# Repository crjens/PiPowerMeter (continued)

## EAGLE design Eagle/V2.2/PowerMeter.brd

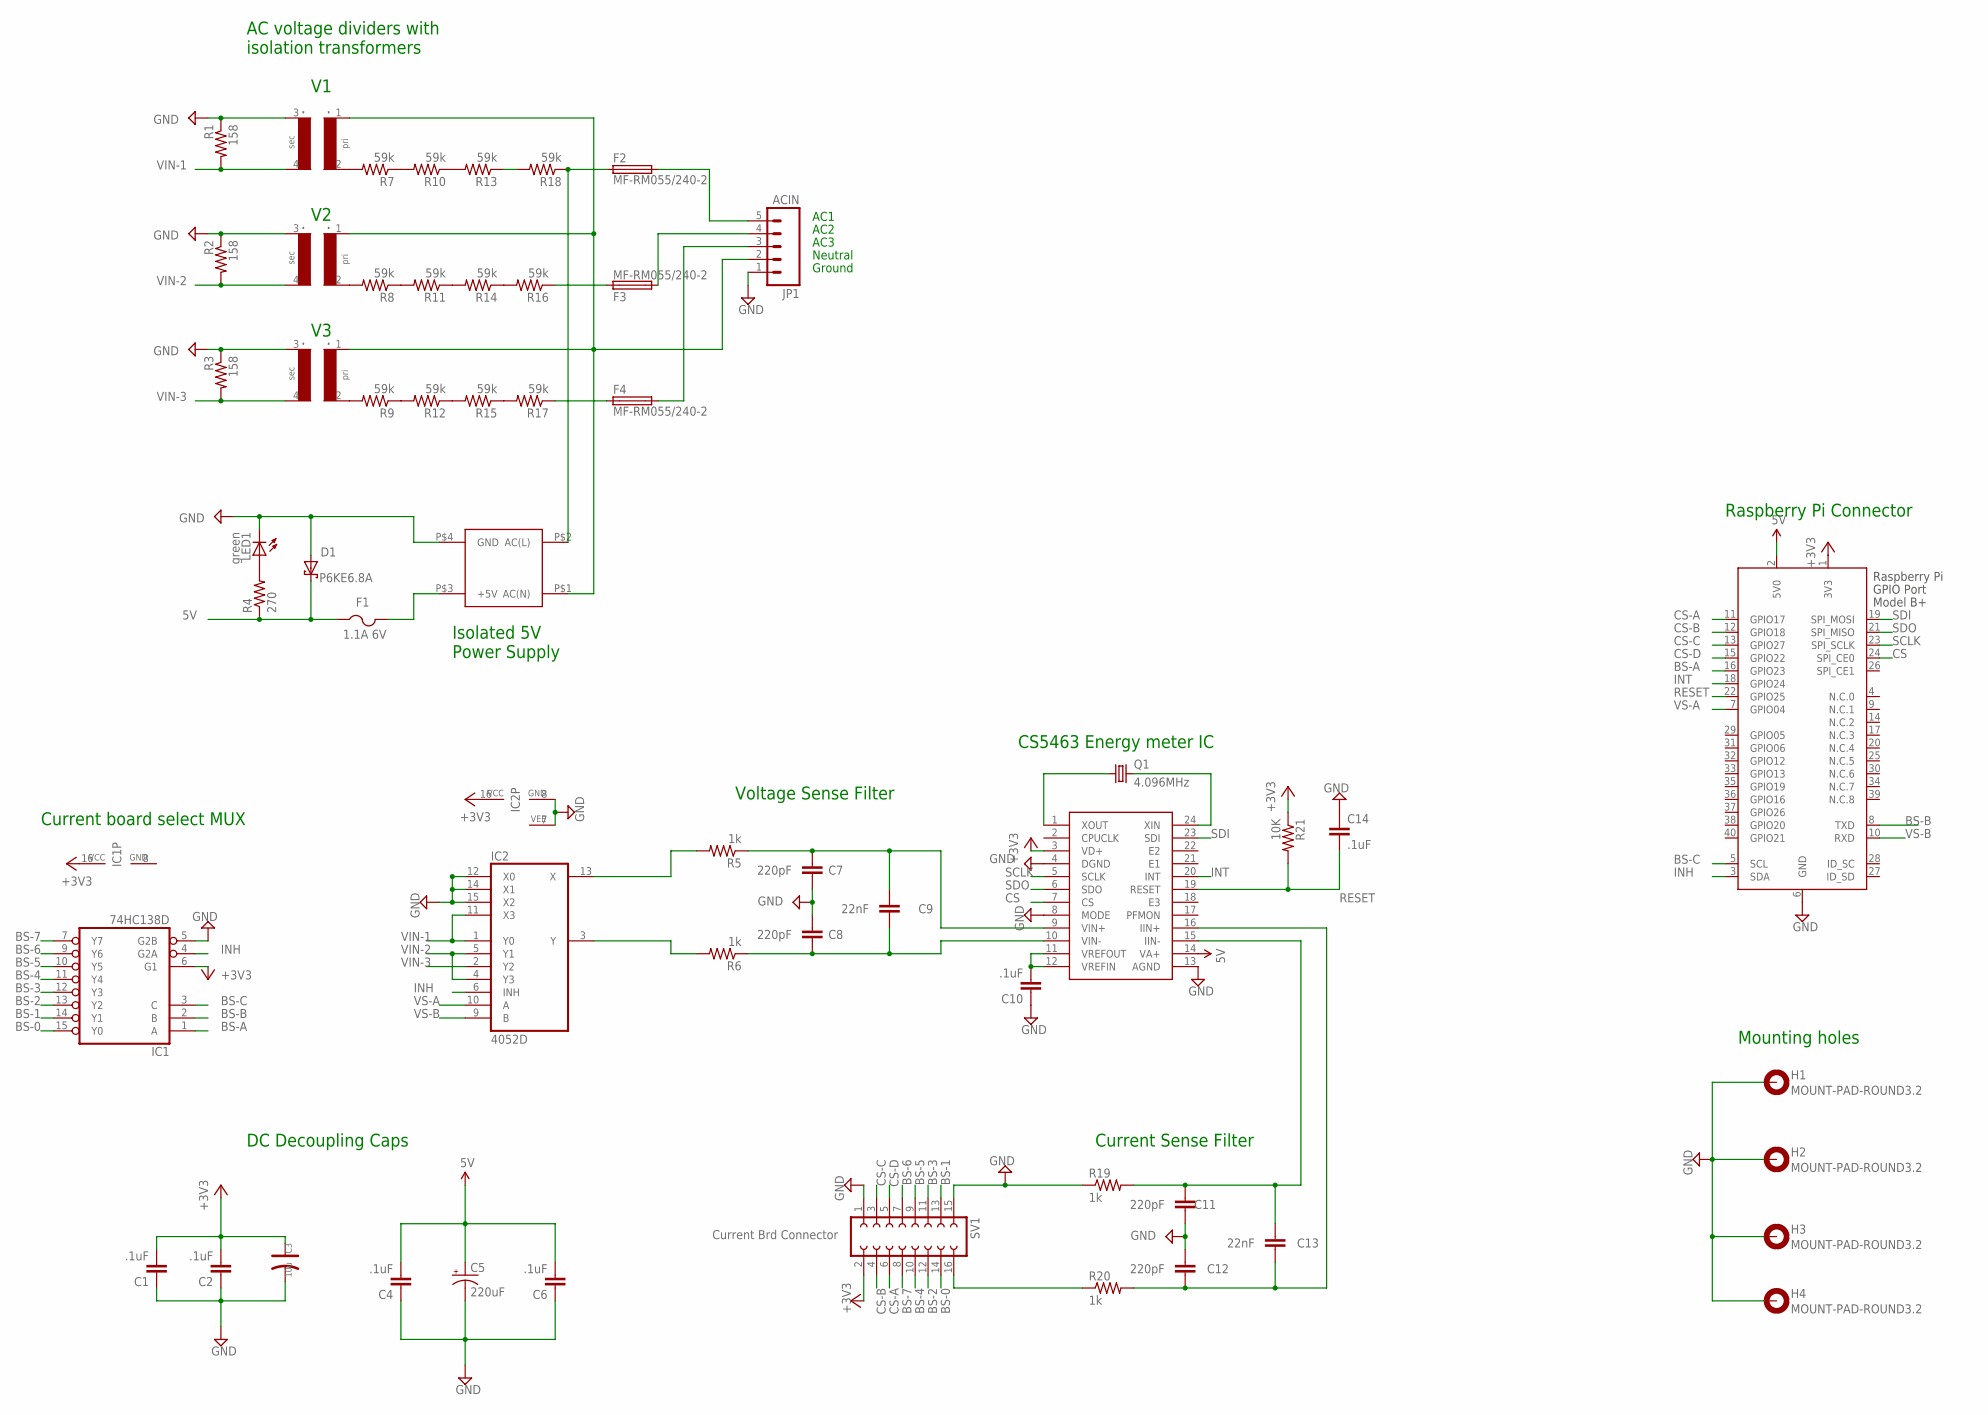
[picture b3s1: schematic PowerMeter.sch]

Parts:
C1, C2, C4, C6, C10, C14: .1uF; C1206; PARTNO C1206C104K5RAC7867
C3: 10u; AVX-C; PARTNO T491C106K016AT
C5: 220uF; E2,5-6E; PARTNO ESH227M016AE3AA
C7, C8, C11, C12: 220pF; C1206; PARTNO C1206C221J5GACTU
C9, C13: 22nF; C1206; PARTNO C1206C223K5RACTU
D1: P6KE6.8A; C1702-15; PARTNO P6KE6.8A
F1: 1.1A 6V; 1812; PARTNO 0ZCC0110AF2C
F2, F3, F4: MF-RM055/240-2; TE5; PARTNO MF-RM055/240-2
H1, H2, H3, H4: MOUNT-PAD-ROUND3.2; 3,2-PAD
IC1: 74HC138D; SO16; PARTNO SN74HC138NSR
IC2: 4052D; SO16; PARTNO CD4052BNSR
IC3: CS5463; SSOP24; PARTNO CS5463-ISZ
JP1: ACIN; SCREWTERMINAL-5MM-5; PARTNO 1935190
LED1: green; LED_1206; PARTNO LTST-C150GKT
PS1: VSK-S10; PARTNO VSK-S5-5UA
Q1: 4.096MHz; HC49/S; PARTNO 9B-4.096MBBK-B
R1, R2, R3: 158; R1206; PARTNO RC1206FR-07158RL
R4: 270; R1206; PARTNO RC1206FR-07270RL
R5, R6, R19, R20: 1k; R1206; PARTNO RC1206FR-071KL
R7, R8, R9, R10, R11, R12, R13, R14, R15, R16, R17, R18: 59k; R1206; PARTNO RC1206FR-071KL
R21: 10K; R1206; PARTNO RC1206FR-0710KL
SV1: Current Brd Connector; FE08-2; PARTNO PPTC082LFBN-RC
T1, T2, T3: TV16E
X1: RASPI_BOARD_B+_E4; RASPI_BOARD_B+_EDGES_4DRILL; PARTNO M20-9762046

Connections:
5V: C4.2, C5.+, C6.2, D1.C, F1.1, IC3.14 (VA+), R4.1, X1.2 (5V0)
+3V3: C1.2, C2.2, C3.+, IC1.6 (G1), IC1.16 (VCC), IC2.16 (VCC), IC3.3 (VD+), R21.1, SV1.2, X1.1 (3V3)
+5V: F1.2, PS1.P$3 (+5V)
AC(L): F2.1, PS1.P$2 (AC(L)), R18.1
AC(N): JP1.2 (4), PS1.P$1 (AC(N)), T1.1, T2.1, T3.1
BS-0: IC1.15 (Y0), SV1.14
BS-1: IC1.14 (Y1), SV1.13
BS-2: IC1.13 (Y2), SV1.12
BS-3: IC1.12 (Y3), SV1.11
BS-4: IC1.11 (Y4), SV1.10
BS-5: IC1.10 (Y5), SV1.9
BS-6: IC1.9 (Y6), SV1.7
BS-7: IC1.7 (Y7), SV1.8
BS-A: IC1.1 (A), X1.16 (GPIO23)
BS-B: IC1.2 (B), X1.8 (TXD)
BS-C: IC1.3 (C), X1.5 (SCL)
C5: C12.1, C13.1, IC3.16 (IIN+), R20.2
CS: IC3.7 (CS), X1.24 (SPI_CE0)
CS-A: SV1.6, X1.11 (GPIO17)
CS-B: SV1.4, X1.12 (GPIO18)
CS-C: SV1.3, X1.13 (GPIO27)
CS-D: SV1.5, X1.15 (GPIO22)
GND: C1.1, C2.1, C3.-, C4.1, C5.-, C6.1, C7.1, C8.2, C10.1, C11.1, C12.2, C14.1, D1.A, H1.B3,2, H2.B3,2, H3.B3,2, H4.B3,2, IC1.5 (G2B), IC1.8 (GND), IC2.7 (VEE), IC2.8 (GND), IC2.12 (X0), IC2.14 (X1), IC2.15 (X2), IC3.4 (DGND), IC3.8 (MODE), IC3.13 (AGND), JP1.1 (5), LED1.C, PS1.P$4 (GND), R1.1, R2.1, R3.1, R19.1, SV1.1, SV1.15, T1.3, T2.3, T3.3, X1.6 (GND)
IIN+: R20.1, SV1.16
INH: IC1.4 (G2A), IC2.6 (INH), X1.3 (SDA)
INT: IC3.20 (INT), X1.18 (GPIO24)
unnamed: IC3.1 (XOUT), Q1.1
unnamed: F3.1, R16.1
unnamed: R7.1, R10.2
unnamed: R10.1, R13.2
unnamed: F4.2, JP1.3
unnamed: R11.1, R14.2
unnamed: LED1.A, R4.2
unnamed: C11.2, C13.2, IC3.15 (IIN-), R19.2
unnamed: F2.2, JP1.5 (1)
unnamed: R15.1, R17.2
unnamed: R9.2, T3.2
unnamed: IC3.24 (XIN), Q1.2
unnamed: R9.1, R12.2
unnamed: R12.1, R15.2
unnamed: R8.2, T2.2
unnamed: R8.1, R11.2
unnamed: C10.2, IC3.11 (VREFOUT), IC3.12 (VREFIN)
unnamed: R14.1, R16.2
unnamed: R7.2, T1.2
unnamed: R13.1, R18.2
unnamed: F4.1, R17.1
unnamed: IC2.13 (X), R5.2
unnamed: F3.2, JP1.4 (2)
unnamed: IC2.3 (Y), R6.2
unnamed: C8.1, C9.1, IC3.10 (VIN-), R6.1
R1: C7.2, C9.2, IC3.9 (VIN+), R5.1
RESET: C14.2, IC3.19 (RESET), R21.2, X1.22 (GPIO25)
SCLK: IC3.5 (SCLK), X1.23 (SPI_SCLK)
SDI: IC3.23 (SDI), X1.19 (SPI_MOSI)
SDO: IC3.6 (SDO), X1.21 (SPI_MISO)
VIN-1: IC2.1 (Y0), IC2.11 (X3), R1.2, T1.4
VIN-2: IC2.4 (Y3), IC2.5 (Y1), R2.2, T2.4
VIN-3: IC2.2 (Y2), R3.2, T3.4
VS-A: IC2.10 (A), X1.7 (GPIO04)
VS-B: IC2.9 (B), X1.10 (RXD)

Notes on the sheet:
AC voltage dividers with isolation transformers
Isolated 5V Power Supply
DC Decoupling Caps
Raspberry Pi Connector
CS5463 Energy meter IC
Voltage Sense Filter
Current Sense Filter
Current board select MUX
Mounting holes
AC1
AC2
AC3
Neutral
Ground

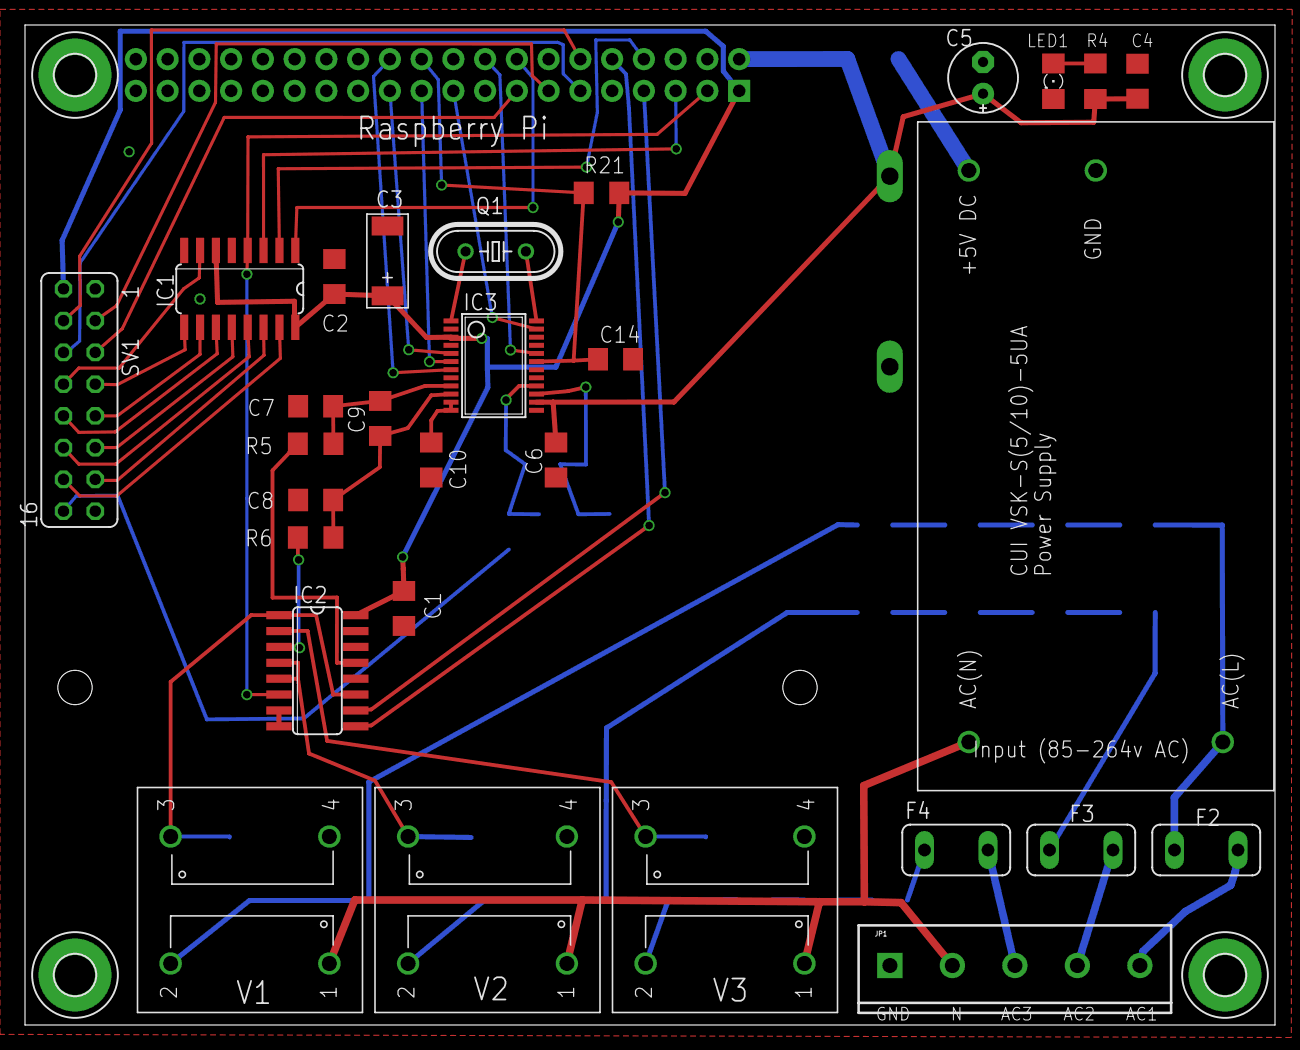
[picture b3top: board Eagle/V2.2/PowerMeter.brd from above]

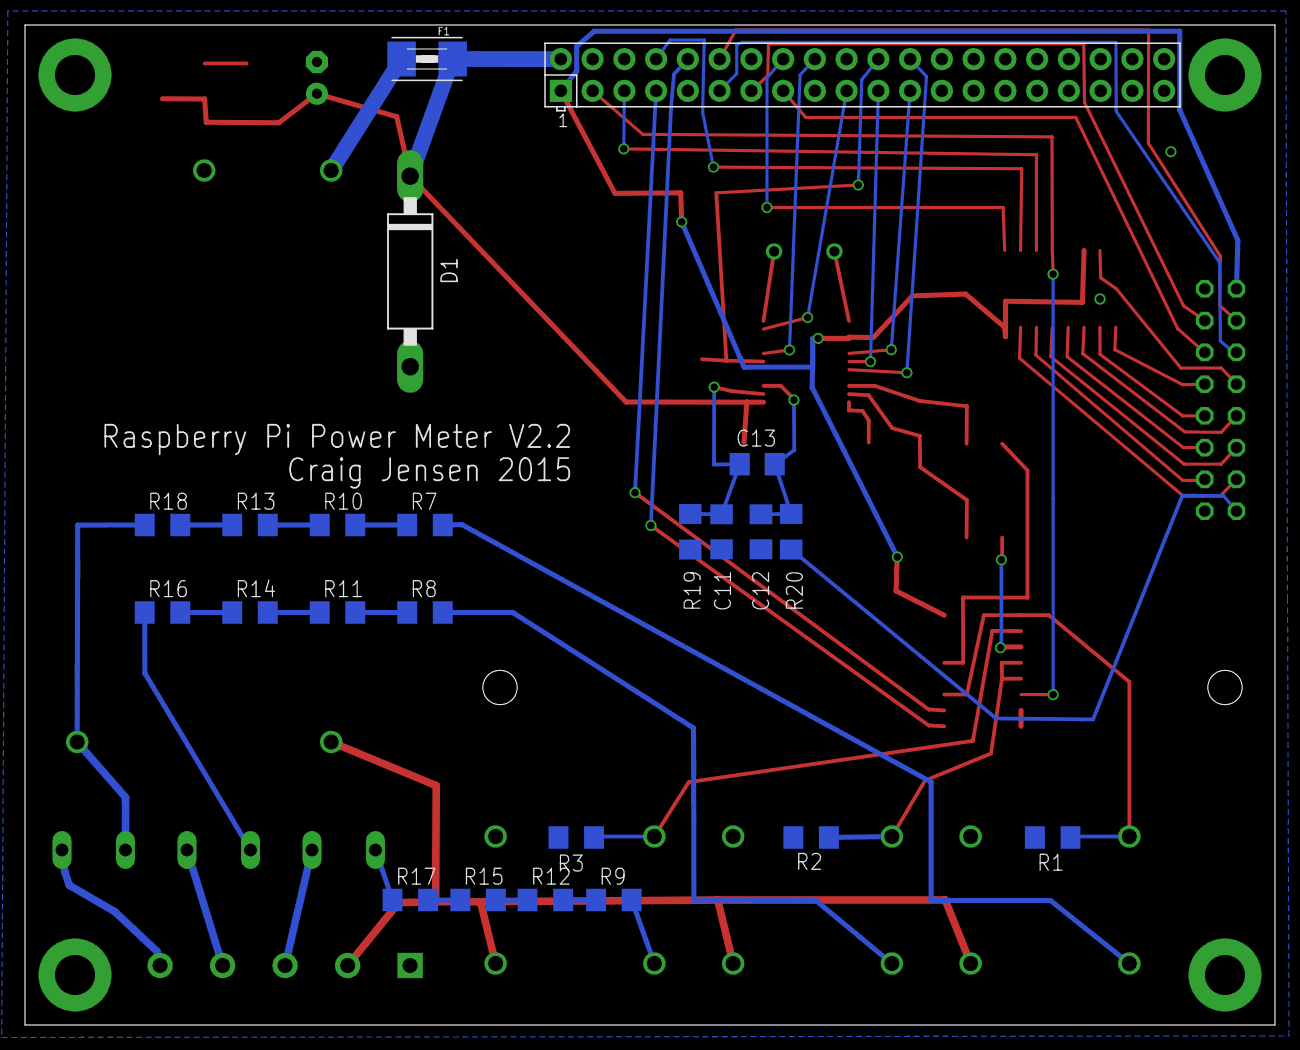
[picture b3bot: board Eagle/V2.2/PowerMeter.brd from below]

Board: 2 copper layers, 100.0 x 80.0 mm, 56 parts (23 on the bottom side), 61 nets.

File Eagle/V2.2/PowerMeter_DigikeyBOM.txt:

Qty Value                 Part Num           Package                     Parts                                                   Mfg Name                    VID Vendor Part Num     Description                      Pkg Code           XREF 
6   .1uF                  C1206C104K5RAC7867 C1206                       C1, C2, C4, C6, C10, C14                                Kemet                       DK  399-1249-1-ND       CAP CER 0.1UF 50V 10% X7R 1206   1206               REF2 
1   1.1A 6V               0ZCC0110AF2C       1812                        F1                                                      Bel Fuse Inc                DK  507-1500-1-ND       PTC RESTTBLE 1.10A 16V CHIP 1812 1812               REF24
4   1k                    RC1206FR-071KL     R1206                       R5, R6, R19, R20                                        Yageo                       DK  311-1.00KFRCT-ND    RES SMD 1K OHM 1% 1/4W 1206      1206               REF8 
1   4.096MHz              9B-4.096MBBK-B     HC49/S                      Q1                                                      TXC CORPORATION             DK  887-1876-ND         CRYSTAL                          4.0960MHZ 20PF T/H 1206 
1   10K                   RC1206FR-0710KL    R1206                       R21                                                     Yageo                       DK  311-10.0KFRCT-ND    RES SMD 10K OHM 1% 1/4W 1206     1206               *    
1   10u                   T491C106K016AT     AVX-C                       C3                                                      Kemet                       DK  399-3732-1-ND       CAP TANT 10UF 16V 10% 2413       AVX-C              REF7 
2   22nF                  C1206C223K5RACTU   C1206                       C9, C13                                                 Kemet                       DK  399-1242-1-ND       CAP CER 0.022UF 50V 10% X7R 1206 1206               REF4 
12  59k                   RC1206FR-071KL     R1206                       R7, R8, R9, R10, R11, R12, R13, R14, R15, R16, R17, R18 Yageo                       DK  311-1.00KFRCT-ND    RES SMD 1K OHM 1% 1/4W 1206      1206               REF8 
1   74HC138D              SN74HC138NSR       SO16                        IC1                                                     Texas Instruments           DK  296-12886-1-ND      IC DECODER/DEMUX 3-8 LINE 16SO   16-SOIC            REF21
3   158                   RC1206FR-07158RL   R1206                       R1, R2, R3                                              Yageo                       DK  311-158FRCT-ND      RES SMD 158 OHM 1% 1/4W 1206     1206               *    
4   220pF                 C1206C221J5GACTU   C1206                       C7, C8, C11, C12                                        Kemet                       DK  399-8167-1-ND       CAP CER 220PF 50V 5% NP0 1206    1206               REF3 
1   220uF                 ESH227M016AE3AA    E2,5-6E                     C5                                                      Kemet                       DK  399-6566-ND         CAP ALUM 220UF 16V 20% RADIAL    Radial, Can        REF6 
1   270                   RC1206FR-07270RL   R1206                       R4                                                      Yageo                       DK  311-270FRCT-ND      RES SMD 270 OHM 1% 1/4W 1206     1206               *    
1   4052D                 CD4052BNSR         SO16                        IC2                                                     Texas Instruments           DK  296-14116-1-ND      IC MUX/DEMUX DUAL 4X1 16SO       16-SOIC            *    
1   ACIN                  1935190            SCREWTERMINAL-5MM-5         JP1                                                     Phoenix Contact             DK  277-1580-ND         TERM BLOCK PCB 5POS 5.0MM GREEN  REF36              *    
1   CS5463                CS5463-ISZ         SSOP24                      IC3                                                     Cirrus Logic Inc            DK  598-1096-5-ND       IC ENERGY METERING 1PHASE 24SSOP 24-SSOP            REF23
1   Current Brd Connector PPTC082LFBN-RC     FE08-2                      SV1                                                     Sullins Connector Solutions DK  S7076-ND            CONN HEADER FMAL 16PS .1" DL TIN REF25              *    
3   MF-RM055/240-2        MF-RM055/240-2     TE5                         F2, F3, F4                                              Bourns Inc.                 DK  MF-RM055/240-2CT-ND PTC RESETTABLE FUSE RADIAL       Radial             REF17
1   P6KE6.8A              P6KE6.8A           C1702-15                    D1                                                      Littelfuse Inc              DK  P6KE6.8ALFCT-ND     TVS DIODE 5.8VWM 10.5VC DO204AC  DO-15              REF18
1   RASPI_BOARD_B+_E4     M20-9762046        RASPI_BOARD_B+_EDGES_4DRILL X1                                                      Harwin Inc                  DK  952-1896-ND         20+20 DIL VERT PIN HDR           REF26              *    
3   TV16E                 *                  TV16E                       T1, T2, T3                                              *                           *   *                   *                                *                  *    
1   VSK-S10               VSK-S5-5UA         VSK-S10                     PS1                                                     CUI Inc                     DK  102-2386-ND         CONV AC/DC 5W 5V 1A PCB          *                  REF20
1   green                 LTST-C150GKT       LED_1206                    LED1                                                    Lite-On Inc                 DK  160-1169-1-ND       LED GREEN CLEAR 1206 SMD         1206               REF19

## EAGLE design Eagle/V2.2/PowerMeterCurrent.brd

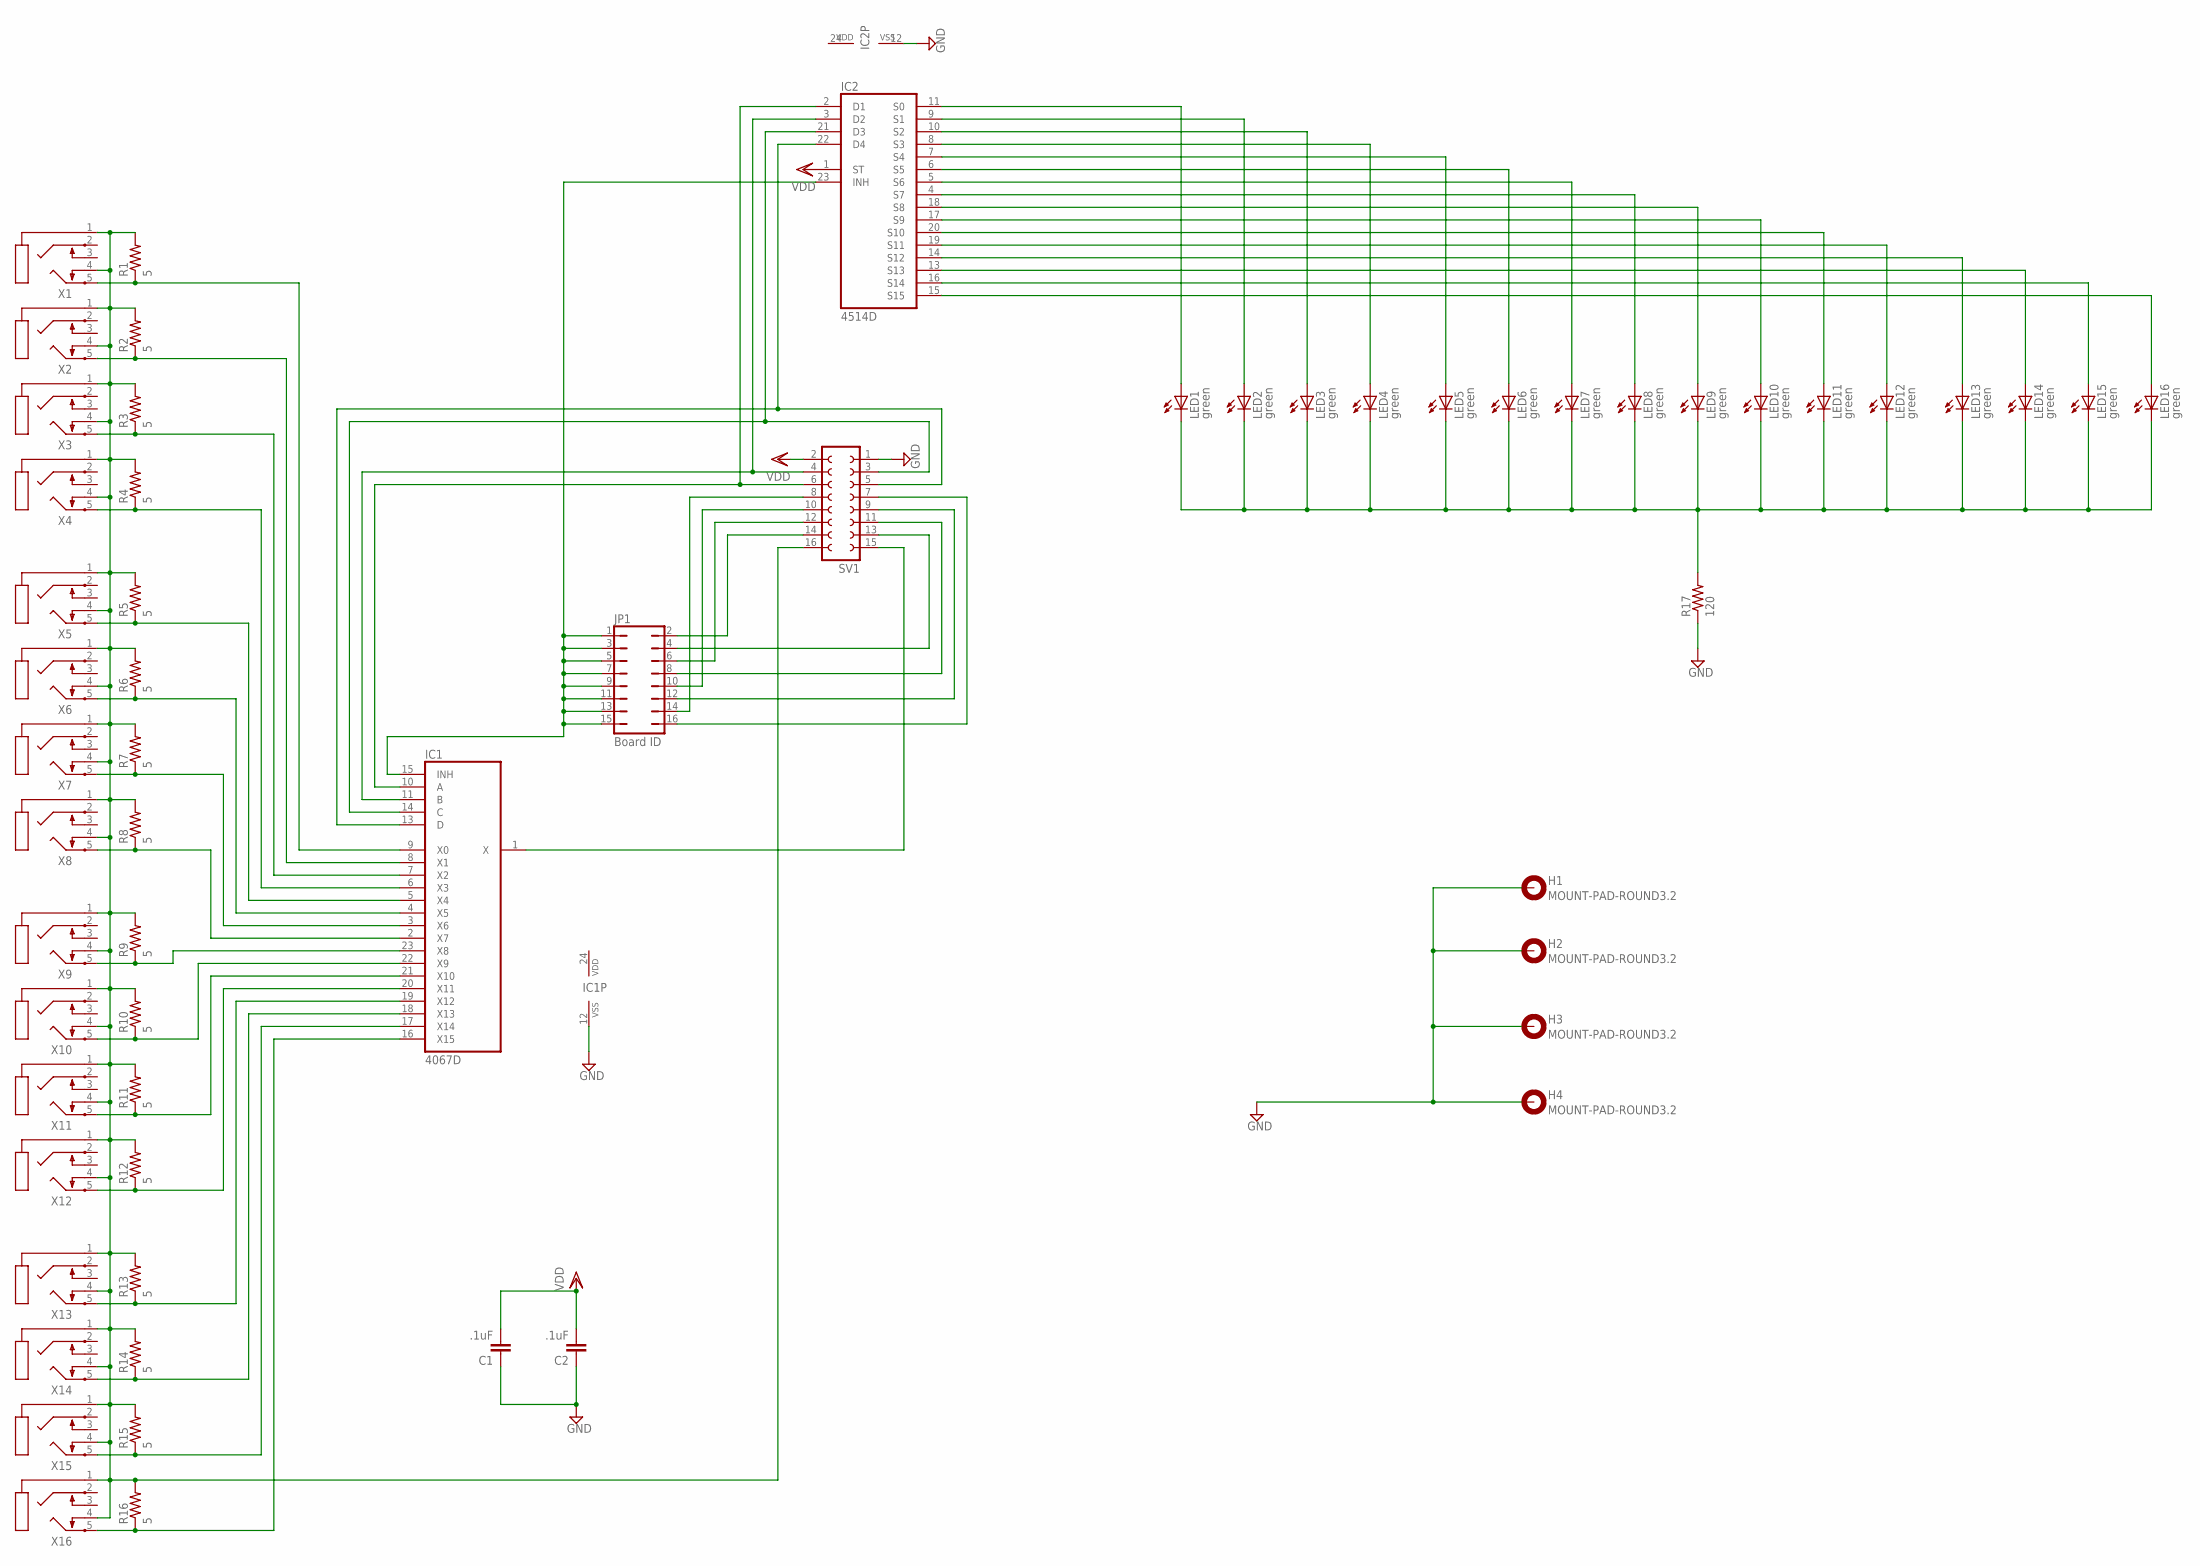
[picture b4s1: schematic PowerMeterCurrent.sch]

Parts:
C1, C2: .1uF; C1206; PARTNO C1206C104K5RAC7867
H1, H2, H3, H4: MOUNT-PAD-ROUND3.2; 3,2-PAD
IC1: 4067D; SO24W; PARTNO 74HC4067D,652
IC2: 4514D; SO24W; PARTNO 74HC4514D,652
JP1: Board ID; JP8Q; PARTNO 67996-416HLF
LED1, LED2, LED3, LED4, LED5, LED6, LED7, LED8, LED9, LED10, LED11, LED12, LED13, LED14, LED15, LED16: green; LED_1206; PARTNO LTST-C150GKT
R1, R2, R3, R4, R5, R6, R7, R8, R9, R10, R11, R12, R13, R14, R15, R16: 5; R1206; PARTNO RC1206FR-075R1L
R17: 120; R1206; PARTNO RC1206FR-07120RL
SV1: FE08-2; PARTNO SSQ-108-02-T-D
X1, X2, X3, X4, X5, X6, X7, X8, X9, X10, X11, X12, X13, X14, X15, X16: STEREOJACK; STX3100; PARTNO SJ1-3525N

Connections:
GND: C1.1, C2.1, H1.B3,2, H2.B3,2, H3.B3,2, H4.B3,2, IC1.12 (VSS), IC2.12 (VSS), R17.1, SV1.1
unnamed: IC1.10 (A), IC2.2 (D1), SV1.6
unnamed: IC2.15 (S15), LED16.A
unnamed: IC1.11 (B), IC2.3 (D2), SV1.4
unnamed: IC1.14 (C), IC2.21 (D3), SV1.3
unnamed: IC1.13 (D), IC2.22 (D4), SV1.5
unnamed: IC1.15 (INH), IC2.23 (INH), JP1.1, JP1.3, JP1.5, JP1.7, JP1.9, JP1.11, JP1.13, JP1.15
unnamed: JP1.14, SV1.8
unnamed: JP1.10, SV1.10
unnamed: IC2.16 (S14), LED15.A
unnamed: JP1.6, SV1.12
unnamed: JP1.2, SV1.14
unnamed: R1.2, R2.2, R3.2, R4.2, R5.2, R6.2, R7.2, R8.2, R9.2, R10.2, R11.2, R12.2, R13.2, R14.2, R15.2, R16.2, SV1.16, X1.1, X1.4, X2.1, X2.4, X3.1, X3.4, X4.1, X4.4, X5.1, X5.4, X6.1, X6.4, X7.1, X7.4, X8.1, X8.4, X9.1, X9.4, X10.1, X10.4, X11.1, X11.4, X12.1, X12.4, X13.1, X13.4, X14.1, X14.4, X15.1, X15.4, X16.1, X16.4
unnamed: JP1.4, SV1.13
unnamed: JP1.8, SV1.11
unnamed: JP1.12, SV1.9
unnamed: JP1.16, SV1.7
unnamed: IC1.1 (X), SV1.15
unnamed: IC1.5 (X4), R5.1, X5.5
unnamed: IC2.13 (S13), LED14.A
unnamed: IC1.9 (X0), R1.1, X1.5
unnamed: LED1.C, LED2.C, LED3.C, LED4.C, LED5.C, LED6.C, LED7.C, LED8.C, LED9.C, LED10.C, LED11.C, LED12.C, LED13.C, LED14.C, LED15.C, LED16.C, R17.2
unnamed: IC1.8 (X1), R2.1, X2.5
unnamed: IC1.7 (X2), R3.1, X3.5
unnamed: IC1.6 (X3), R4.1, X4.5
unnamed: IC1.4 (X5), R6.1, X6.5
unnamed: IC1.3 (X6), R7.1, X7.5
unnamed: IC1.2 (X7), R8.1, X8.5
unnamed: IC1.23 (X8), R9.1, X9.5
unnamed: IC2.14 (S12), LED13.A
unnamed: IC2.19 (S11), LED12.A
unnamed: IC2.20 (S10), LED11.A
unnamed: IC2.17 (S9), LED10.A
unnamed: IC2.18 (S8), LED9.A
unnamed: IC2.4 (S7), LED8.A
unnamed: IC2.5 (S6), LED7.A
unnamed: IC2.6 (S5), LED6.A
unnamed: IC2.7 (S4), LED5.A
unnamed: IC2.8 (S3), LED4.A
unnamed: IC1.22 (X9), R10.1, X10.5
unnamed: IC1.21 (X10), R11.1, X11.5
unnamed: IC2.10 (S2), LED3.A
unnamed: IC2.9 (S1), LED2.A
unnamed: IC2.11 (S0), LED1.A
unnamed: IC1.20 (X11), R12.1, X12.5
unnamed: IC1.18 (X13), R14.1, X14.5
unnamed: IC1.17 (X14), R15.1, X15.5
unnamed: IC1.19 (X12), R13.1, X13.5
unnamed: IC1.16 (X15), R16.1, X16.5
VDD: C1.2, C2.2, IC1.24 (VDD), IC2.1 (ST), IC2.24 (VDD), SV1.2

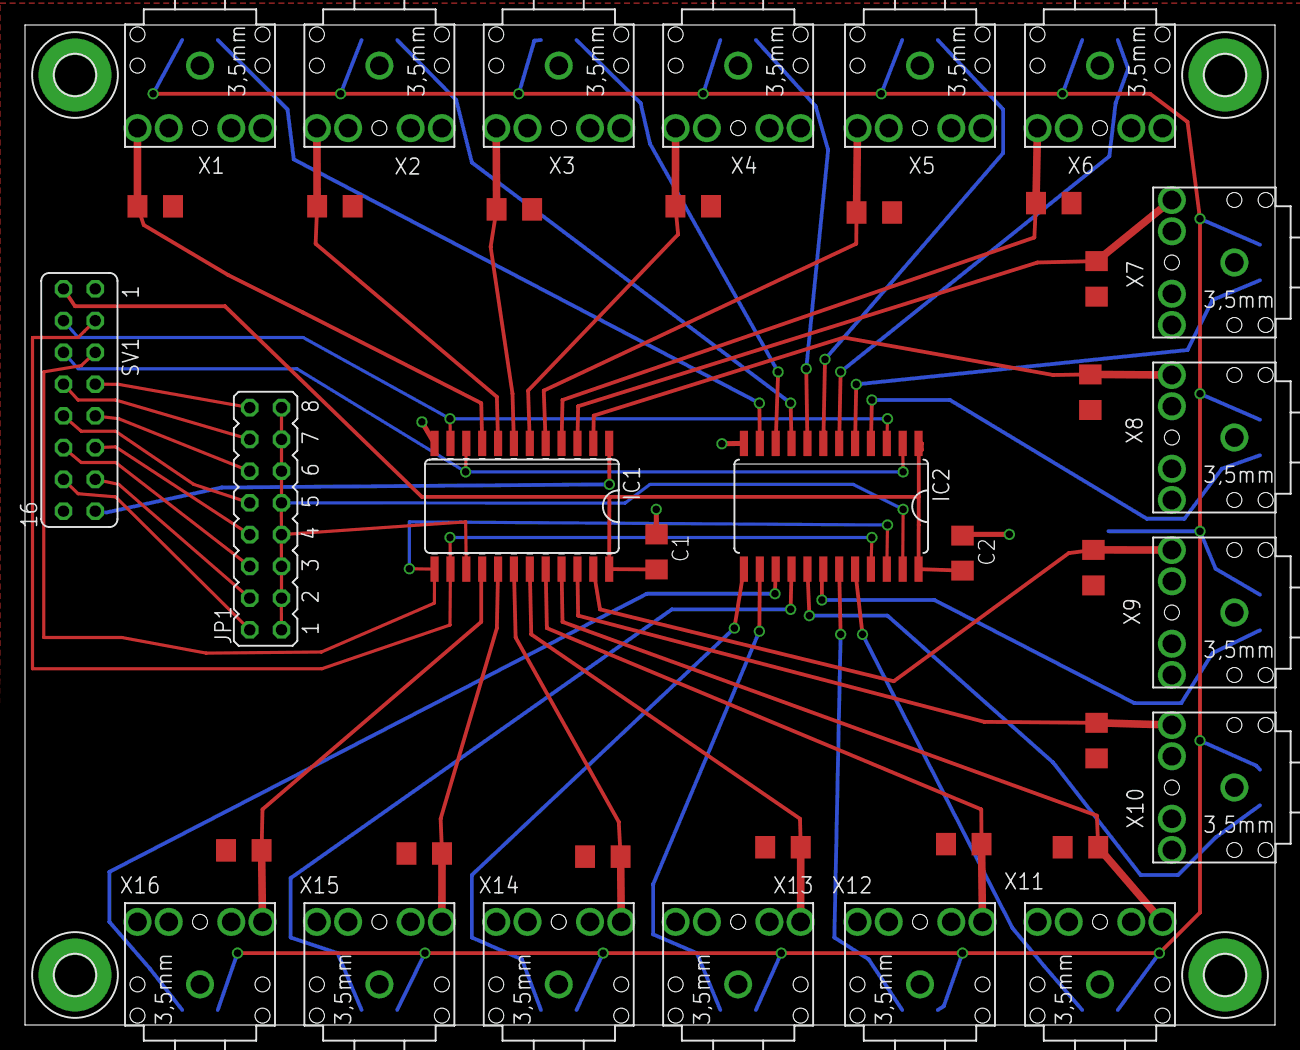
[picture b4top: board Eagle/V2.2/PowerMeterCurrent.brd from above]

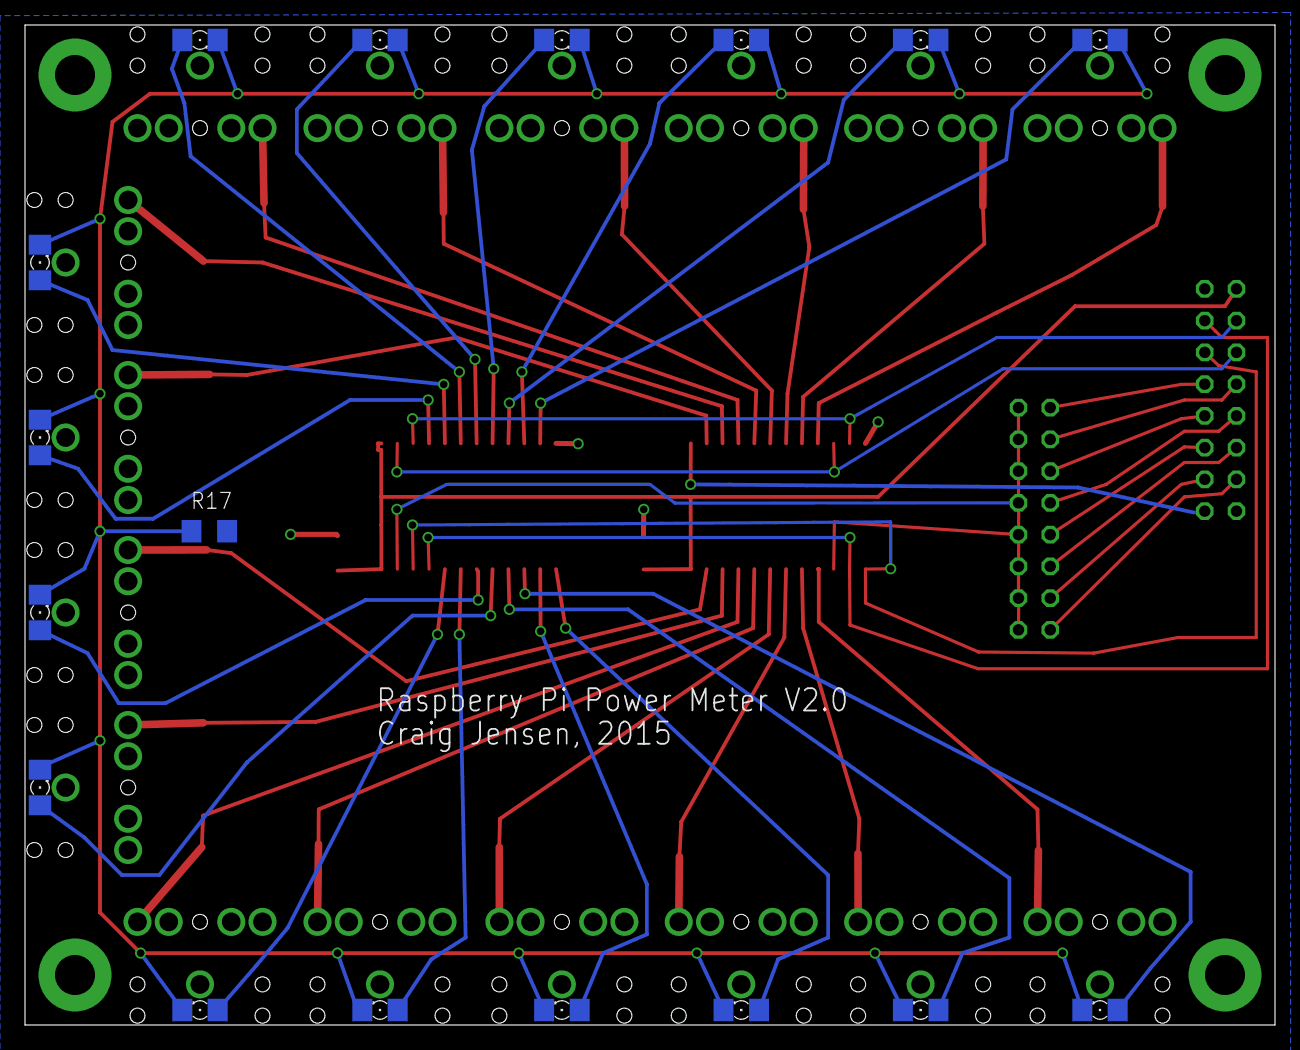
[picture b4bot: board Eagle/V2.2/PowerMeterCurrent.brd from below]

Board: 2 copper layers, 100.0 x 80.0 mm, 59 parts (17 on the bottom side), 50 nets.
